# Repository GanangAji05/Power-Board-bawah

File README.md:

# Power-Board-bawah

Design PCB

Design 3D

Check signal PWM

Testing Motor and code

https://github.com/user-attachments/assets/2eb00f5d-e821-4132-b0ed-e6486bcefb03

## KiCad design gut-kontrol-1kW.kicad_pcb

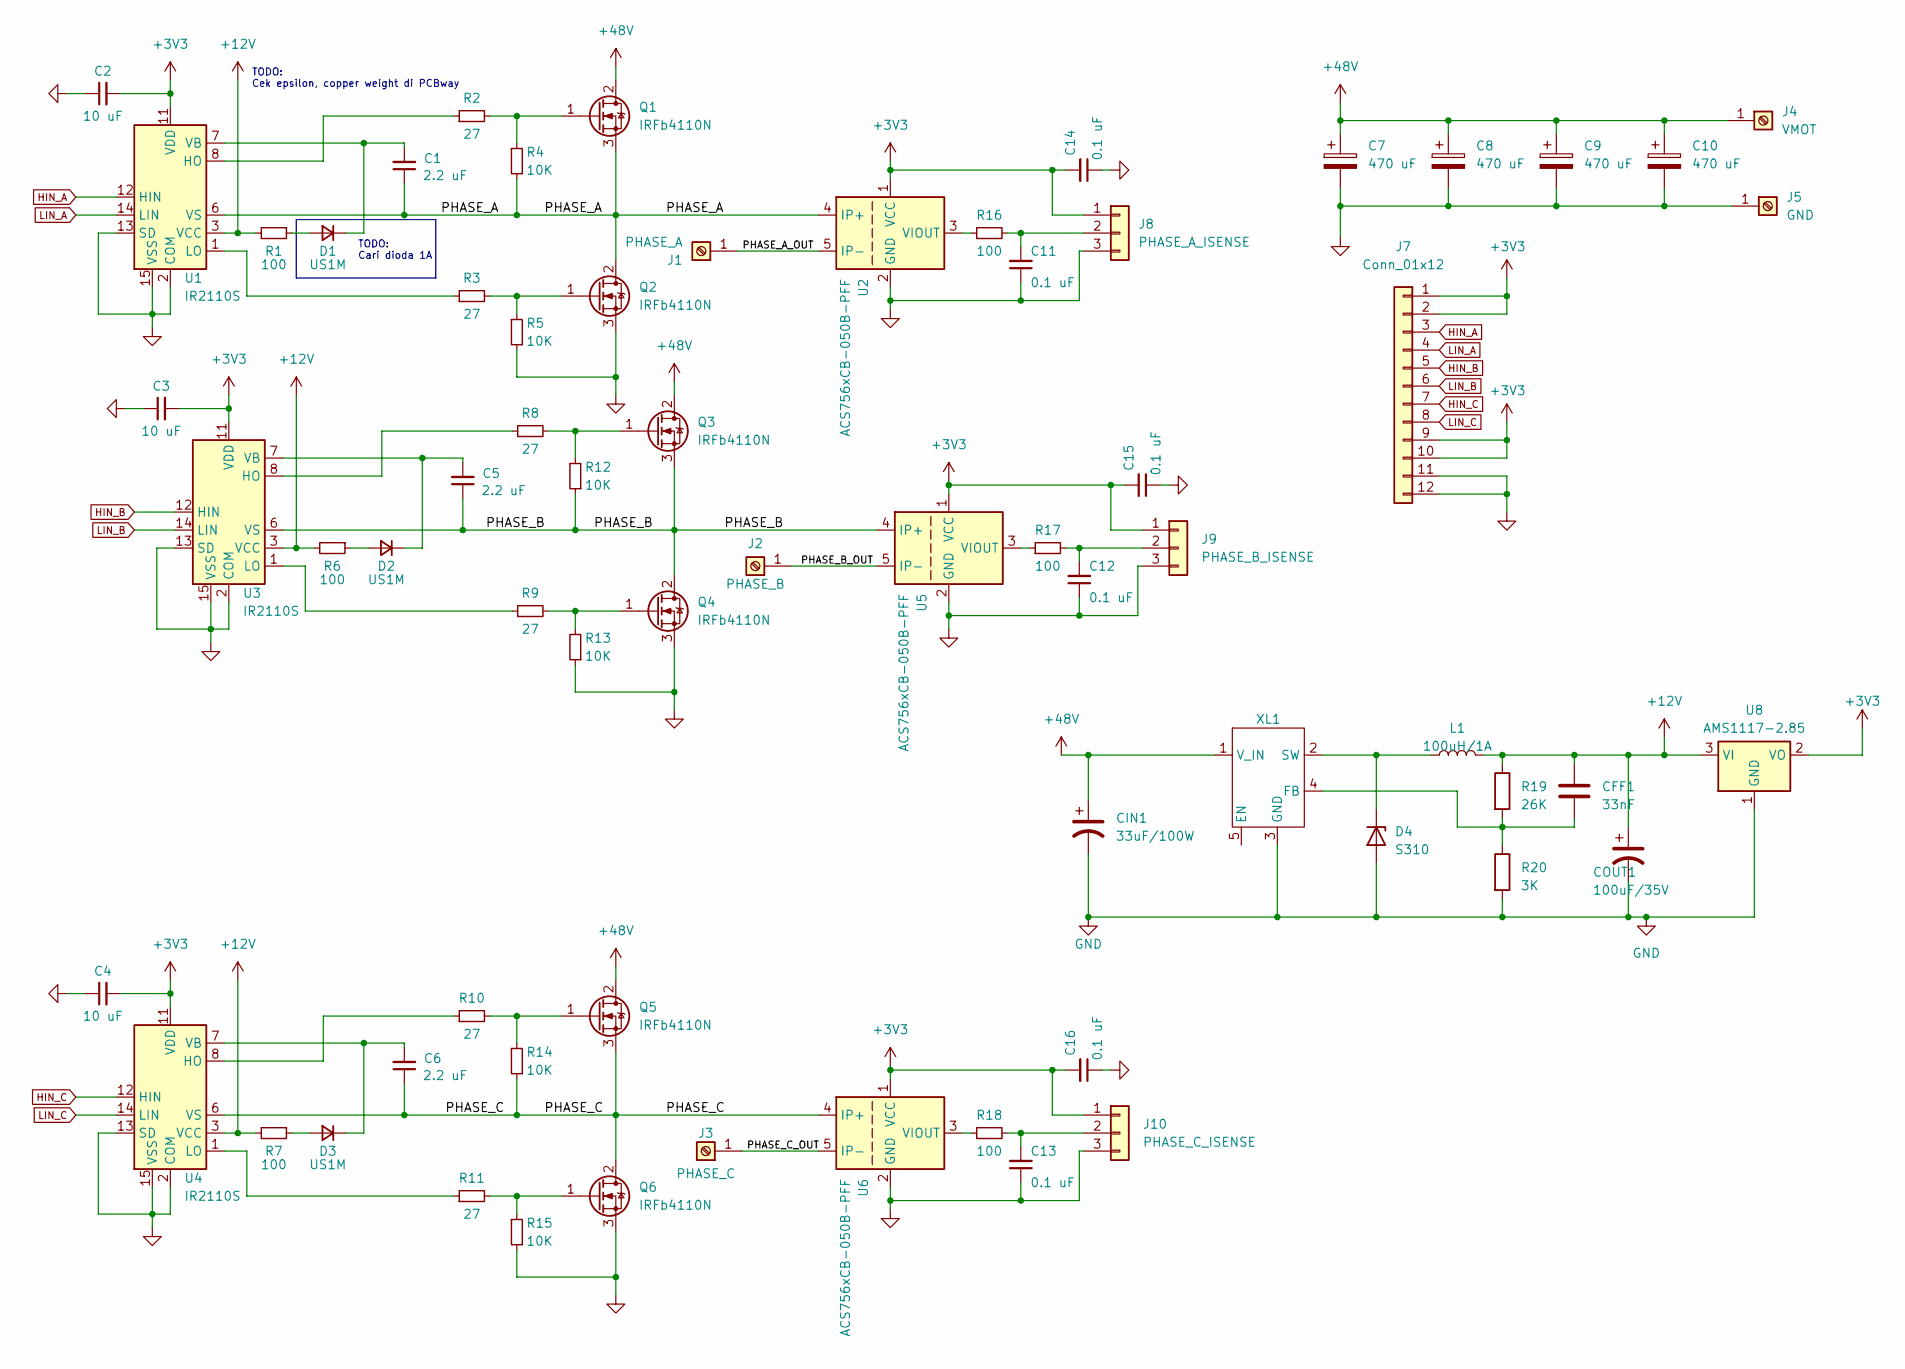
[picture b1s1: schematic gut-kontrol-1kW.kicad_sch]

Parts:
C1, C5, C6: 2.2 uF; C_0805_2012Metric_Pad1.18x1.45mm_HandSolder
C2, C3, C4: 10 uF; C_0805_2012Metric_Pad1.18x1.45mm_HandSolder
C7, C8, C9, C10: 470 uF; CP_Radial_D16.0mm_P7.50mm
C11, C12, C13, C14, C15, C16: 0.1 uF; C_0805_2012Metric_Pad1.18x1.45mm_HandSolder
CFF1: 33nF; R_0805_2012Metric
CIN1: 33uF/100W; CP_Radial_D8.0mm_P3.50mm
COUT1: 100uF/35V; CP_Radial_D8.0mm_P3.50mm
D1, D2, D3: US1M; D_SMA
D4: S310; D_SMA
J1: PHASE_A; MountingHole_3.2mm_M3_DIN965_Pad
J2: PHASE_B; MountingHole_3.2mm_M3_DIN965_Pad
J3: PHASE_C; MountingHole_3.2mm_M3_DIN965_Pad
J4: VMOT; MountingHole_3.2mm_M3_DIN965_Pad
J5: GND; MountingHole_3.2mm_M3_DIN965_Pad
J7: Conn_01x12; PinHeader_2x06_P2.54mm_Vertical
J8: PHASE_A_ISENSE; PinSocket_1x03_P2.54mm_Vertical
J9: PHASE_B_ISENSE; PinSocket_1x03_P2.54mm_Vertical
J10: PHASE_C_ISENSE; PinSocket_1x03_P2.54mm_Vertical
L1: 100uH/1A; L_10.4x10.4_H4.8
Q1, Q2, Q3, Q4, Q5, Q6: IRFb4110N; TO-220-3_Vertical
R1, R6, R7, R16, R17, R18: 100; R_0805_2012Metric_Pad1.20x1.40mm_HandSolder
R2, R3, R8, R9, R10, R11: 27; R_0805_2012Metric_Pad1.20x1.40mm_HandSolder
R4, R5, R12, R13, R14, R15: 10K; R_0805_2012Metric_Pad1.20x1.40mm_HandSolder
R19: 26K; R_0805_2012Metric
R20: 3K; R_0805_2012Metric
U1, U3, U4: IR2110S; SOIC-16W_7.5x10.3mm_P1.27mm
U2, U5, U6: ACS756xCB-050B-PFF; Allegro_CB_PFF
U8: AMS1117-2.85; SOT-223-3_TabPin2
XL1: TO-252-5_TabPin3

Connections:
+3V3: C2.2, C3.2, C4.2, C14.2, C15.2, C16.2, J7.1, J7.2, J7.9, J7.10, J8.1, J9.1, J10.1, U1.11 (VDD), U2.1 (VCC), U3.11 (VDD), U4.11 (VDD), U5.1 (VCC), U6.1 (VCC), U8.2 (VO)
+12V: CFF1.1, COUT1.1, L1.2, R1.2, R6.2, R7.2, R19.1, U1.3 (VCC), U3.3 (VCC), U4.3 (VCC), U8.3 (VI)
+48V: C7.1, C8.1, C9.1, C10.1, CIN1.1, J4.1, Q1.2 (D), Q3.2 (D), Q5.2 (D), XL1.1 (V_IN)
/PHASE_A: C1.1, Q1.3 (S), Q2.2 (D), R4.1, U1.6 (VS), U2.4 (IP+)
/PHASE_A_OUT: J1.1, U2.5 (IP-)
/PHASE_B: C5.1, Q3.3 (S), Q4.2 (D), R12.1, U3.6 (VS), U5.4 (IP+)
/PHASE_B_OUT: J2.1, U5.5 (IP-)
/PHASE_C: C6.1, Q5.3 (S), Q6.2 (D), R14.1, U4.6 (VS), U6.4 (IP+)
/PHASE_C_OUT: J3.1, U6.5 (IP-)
GND: C2.1, C3.1, C4.1, C7.2, C8.2, C9.2, C10.2, C11.1, C12.1, C13.1, C14.1, C15.1, C16.1, CIN1.2, COUT1.2, D4.2 (A), J5.1, J7.11, J7.12, J8.3, J9.3, J10.3, Q2.3 (S), Q4.3 (S), Q6.3 (S), R5.1, R13.1, R15.1, R20.2, U1.2 (COM), U1.13 (SD), U1.15 (VSS), U2.2 (GND), U3.2 (COM), U3.13 (SD), U3.15 (VSS), U4.2 (COM), U4.13 (SD), U4.15 (VSS), U5.2 (GND), U6.2 (GND), U8.1 (GND), XL1.3 (GND)
HIN_A: J7.3, U1.12 (HIN)
HIN_B: J7.5, U3.12 (HIN)
HIN_C: J7.7, U4.12 (HIN)
LIN_A: J7.4, U1.14 (LIN)
LIN_B: J7.6, U3.14 (LIN)
LIN_C: J7.8, U4.14 (LIN)
unnamed: D1.2 (A), R1.1
unnamed: C1.2, D1.1 (K), U1.7 (VB)
unnamed: D2.2 (A), R6.1
unnamed: C5.2, D2.1 (K), U3.7 (VB)
unnamed: D3.2 (A), R7.1
unnamed: C6.2, D3.1 (K), U4.7 (VB)
unnamed: D4.1 (K), L1.1, XL1.2 (SW)
unnamed: C11.2, J8.2, R16.2
unnamed: C12.2, J9.2, R17.2
unnamed: C13.2, J10.2, R18.2
unnamed: Q1.1 (G), R2.2, R4.2
unnamed: Q2.1 (G), R3.2, R5.2
unnamed: Q3.1 (G), R8.2, R12.2
unnamed: Q4.1 (G), R9.2, R13.2
unnamed: Q5.1 (G), R10.2, R14.2
unnamed: Q6.1 (G), R11.2, R15.2
unnamed: R2.1, U1.8 (HO)
unnamed: R3.1, U1.1 (LO)
unnamed: R16.1, U2.3 (VIOUT)
unnamed: R8.1, U3.8 (HO)
unnamed: R9.1, U3.1 (LO)
unnamed: R10.1, U4.8 (HO)
unnamed: R11.1, U4.1 (LO)
unnamed: R17.1, U5.3 (VIOUT)
unnamed: R18.1, U6.3 (VIOUT)
unnamed: CFF1.2, R19.2, R20.1, XL1.4 (FB)

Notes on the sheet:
TODO: Cek epsilon, copper weight di PCBway
TODO: Cari dioda 1A

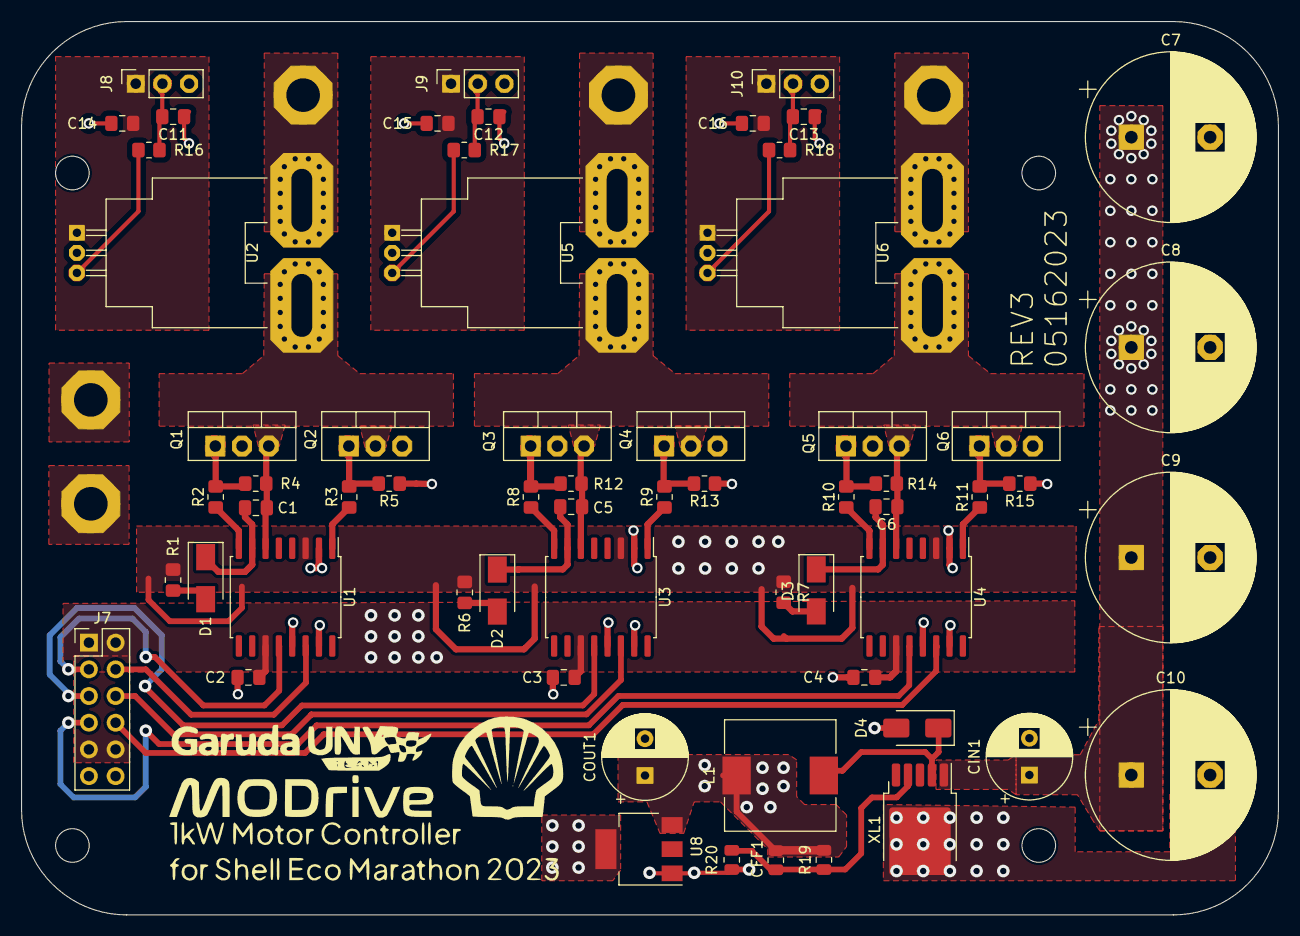
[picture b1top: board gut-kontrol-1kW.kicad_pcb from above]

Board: 2 copper layers, 119.6 x 85.0 mm, 67 parts (0 on the bottom side), 42 nets.

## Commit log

2023-01-03 Project Init
2023-01-04 Done with the powerstage
2023-01-07 done with powerstage board
2023-01-08 Adding connector and CAD viz
2023-01-12 some minor fix
2023-05-12 major fix in conn footprint, bootsrap error, etc
2023-05-14 Nambah Skematik
2023-05-14 nambah footprint dikit
2023-05-14 ganti heatsink
2023-05-15 Layout PCB
2023-05-16 adding artwork
2023-05-16 revisi power plane + logo
2023-05-16 fixing thermal to solid in sensor
2023-05-16 nambah rev number
2023-05-18 adding cad export
2023-11-20 commit 1
